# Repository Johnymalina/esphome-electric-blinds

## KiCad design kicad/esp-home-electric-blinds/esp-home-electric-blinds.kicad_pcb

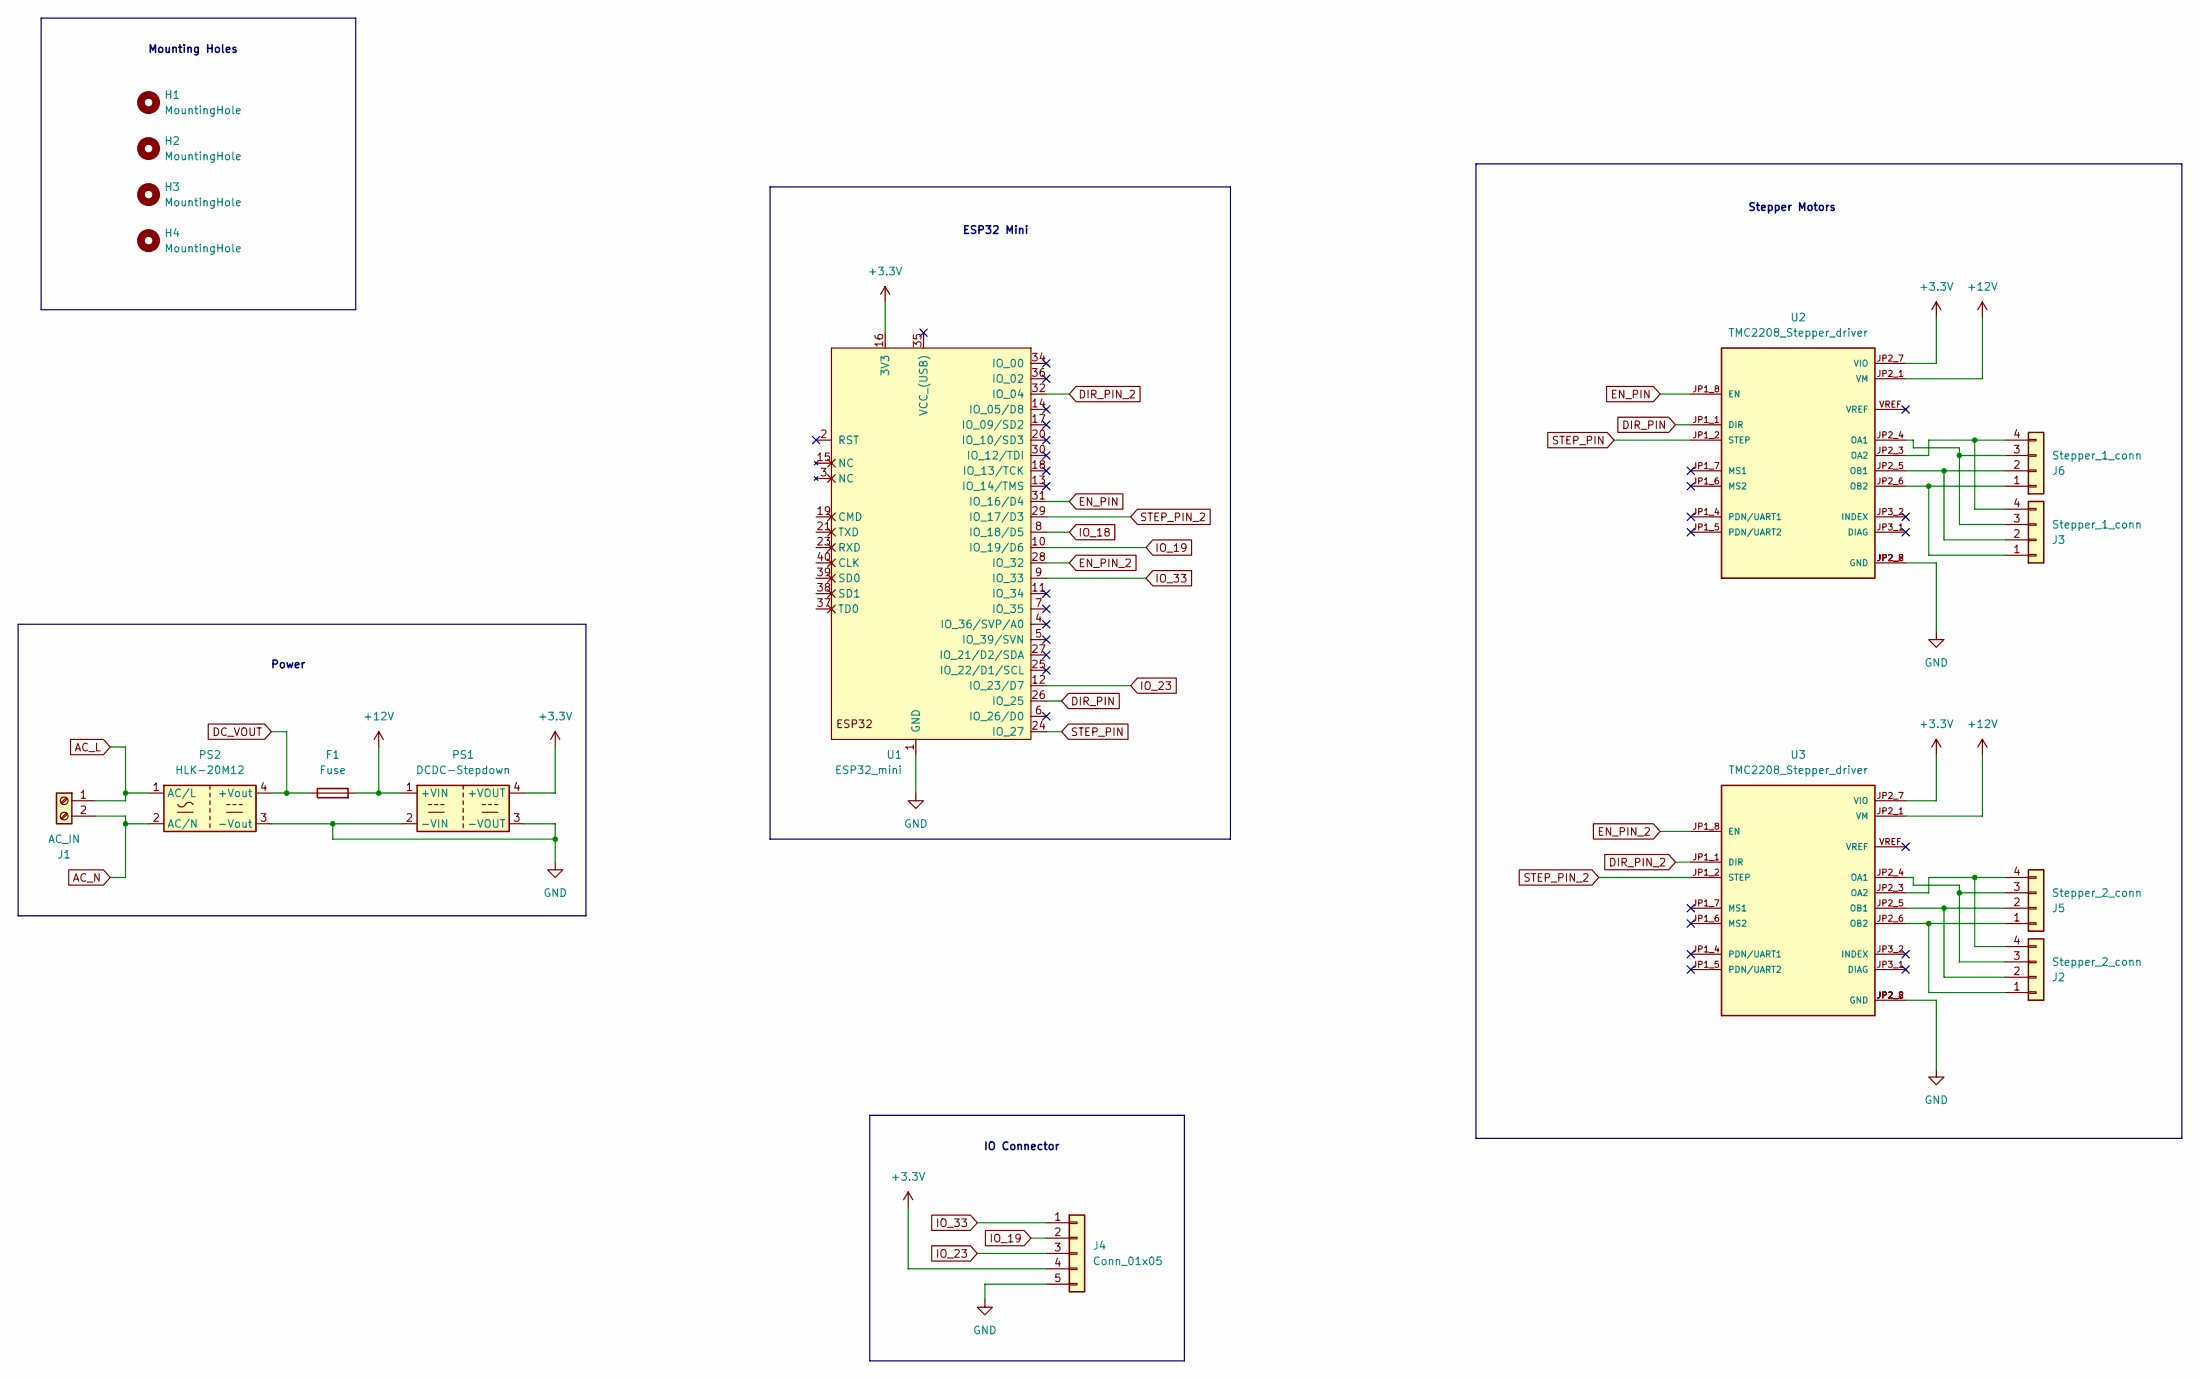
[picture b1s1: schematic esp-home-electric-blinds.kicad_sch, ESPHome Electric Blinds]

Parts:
F1: Fuse; car_fuse_holder
H1, H2, H3, H4: MountingHole; MountingHole_2.7mm_M2.5
J1: AC_IN; ScrewTerminal_01x02
J2, J5: Stepper_2_conn; JST_smd_1x04_horizontal
J3, J6: Stepper_1_conn; JST_smd_1x04_horizontal
J4: Conn_01x05; JST_smd_1x05_horizontal
PS1: DCDC-Stepdown; DCDC_stepdown_module
PS2: HLK-20M12; HLK_AC_DC_20W
U1: ESP32_mini
U2, U3: TMC2208_Stepper_driver; TMC2208_Module

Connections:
+3.3V: J4.4, PS1.4 (+VOUT), U1.16 (3V3), U2.JP2_7 (VIO), U3.JP2_7 (VIO)
+12V: F1.2, PS1.1 (+VIN), U2.JP2_1 (VM), U3.JP2_1 (VM)
AC_L: J1.1, PS2.1 (AC/L)
AC_N: J1.2, PS2.2 (AC/N)
DC_VOUT: F1.1, PS2.4 (+Vout)
DIR_PIN: U1.26 (IO_25), U2.JP1_1 (DIR)
DIR_PIN_2: U1.32 (IO_04), U3.JP1_1 (DIR)
EN_PIN: U1.31 (IO_16/D4), U2.JP1_8 (EN)
EN_PIN_2: U1.28 (IO_32), U3.JP1_8 (EN)
GND: J4.5, PS1.2 (-VIN), PS1.3 (-VOUT), PS2.3 (-Vout), U1.1 (GND), U1.22 (GND), U1.33 (GND), U2.JP2_2 (GND), U2.JP2_8 (GND), U3.JP2_2 (GND), U3.JP2_8 (GND)
IO_18: U1.8 (IO_18/D5)
IO_19: J4.2, U1.10 (IO_19/D6)
IO_23: J4.3, U1.12 (IO_23/D7)
IO_33: J4.1, U1.9 (IO_33)
unnamed: J2.1, J5.1, U3.JP2_6 (OB2)
unnamed: J2.2, J5.2, U3.JP2_5 (OB1)
unnamed: J2.3, J5.3, U3.JP2_4 (OA1)
unnamed: J2.4, J5.4, U3.JP2_3 (OA2)
unnamed: J3.1, J6.1, U2.JP2_6 (OB2)
unnamed: J3.2, J6.2, U2.JP2_5 (OB1)
unnamed: J3.3, J6.3, U2.JP2_4 (OA1)
unnamed: J3.4, J6.4, U2.JP2_3 (OA2)
STEP_PIN: U1.24 (IO_27), U2.JP1_2 (STEP)
STEP_PIN_2: U1.29 (IO_17/D3), U3.JP1_2 (STEP)

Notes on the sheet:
Stepper Motors
Mounting Holes
Power
IO Connector
ESP32 Mini

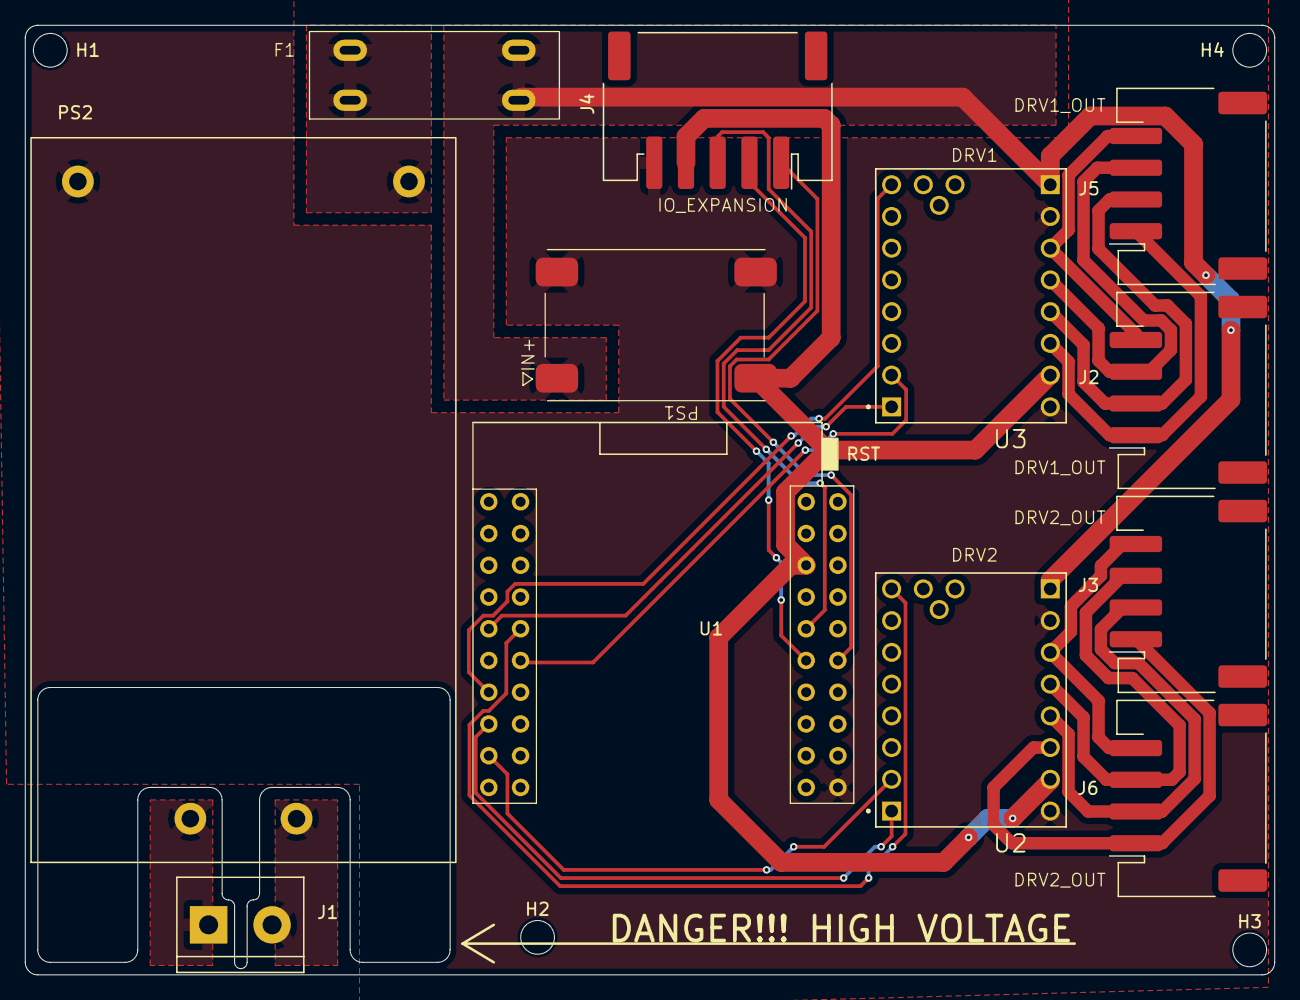
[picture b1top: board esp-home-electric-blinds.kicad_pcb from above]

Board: 2 copper layers, 100.0 x 76.0 mm, 16 parts (0 on the bottom side), 23 nets.

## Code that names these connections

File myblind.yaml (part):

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
  
  speed: 1500 steps/s # Set the speed of the motor
  en_pin: "16"

  mystepper: my_stepper # Name of the stepper motor (leave as is)
  reportin: "0" # Set if you want the blind to report position while moving (causes delay)  
  step_pin: "27" # Swap these \_ coil a
  dir_pin: "25" # Swap these /

  mystepper_2: my_stepper_2 # Name of the stepper motor (leave as is)
  reportin_2: "0" # Set if you want the blind to report position while moving (causes delay)
  step_pin_2: "17"
  dir_pin_2: "4"  
# NOTE:  If you find that your shades are going the wrong way, you can change the pin
#        settings or reverse the + and – wires for each of the A and B motor
#        pairs on your driver and the motor will spin in the opposite direction.
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stepper:
  - platform: a4988
    id: $mystepper
    step_pin: $step_pin
    dir_pin:
      number: $dir_pin
      inverted: true
    max_speed: ${speed}
    # Optional:
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
  - platform: a4988
    id: $mystepper_2
    step_pin: $step_pin_2
    dir_pin:
      number: $dir_pin_2
      inverted: true
    max_speed: ${speed}
    # Optional:
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  - platform: gpio
    name: Steppers Enabled
    pin:
      number: $en_pin
      inverted: True
    restore_mode: RESTORE_DEFAULT_ON

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
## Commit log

2024-03-24 edited to fit tmc2209
2024-03-24 sleep rm
2024-03-24 added stepper
2024-03-24 added second blind
2024-03-25 added kicad project
2024-03-25 kicad gitignore
2024-03-25 pcb add and sch
2024-03-25 changed board
2024-03-25 power sch added
2024-03-25 stepper config
2024-03-25 changed step pin
2024-03-25 esp32 added
2024-03-25 added steppers
2024-03-25 added stepper connector
2024-03-25 added IO connector
2024-03-25 rearange
2024-03-25 assigned footprints
2024-03-25 mounting holes
2024-03-25 pcb layout
2024-03-25 added AC nets
2024-03-25 power lines
2024-03-26 pcb v2
2024-03-26 signed
2024-03-26 esp32 edit?
2024-06-22 stepper pinout switch
2024-06-22 stepper connection update
2024-06-24 silkscreen description
2024-06-24 added high voltage warning
